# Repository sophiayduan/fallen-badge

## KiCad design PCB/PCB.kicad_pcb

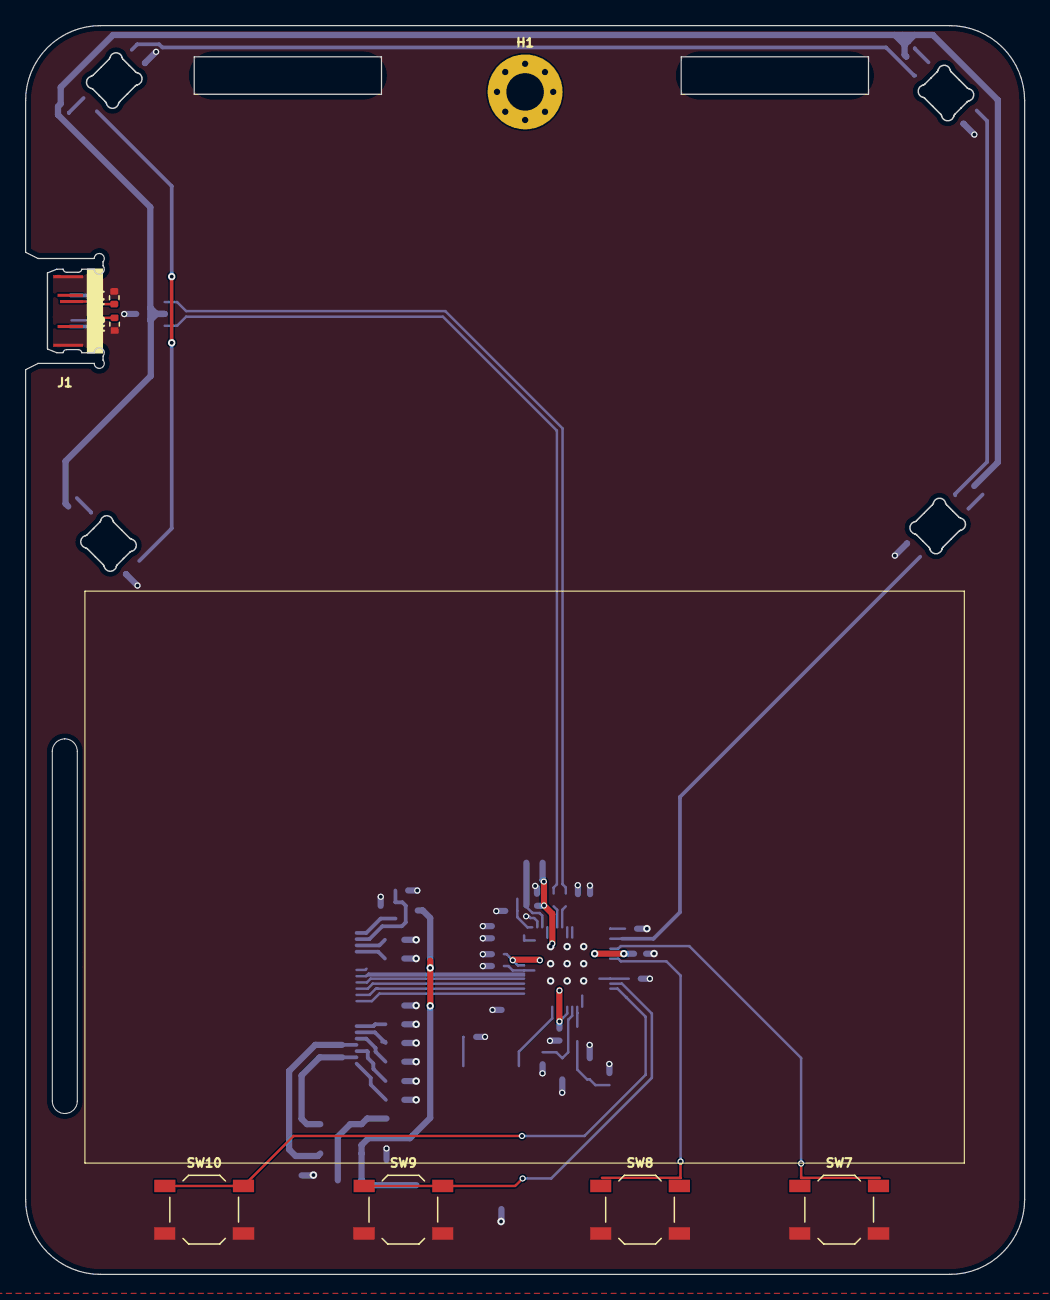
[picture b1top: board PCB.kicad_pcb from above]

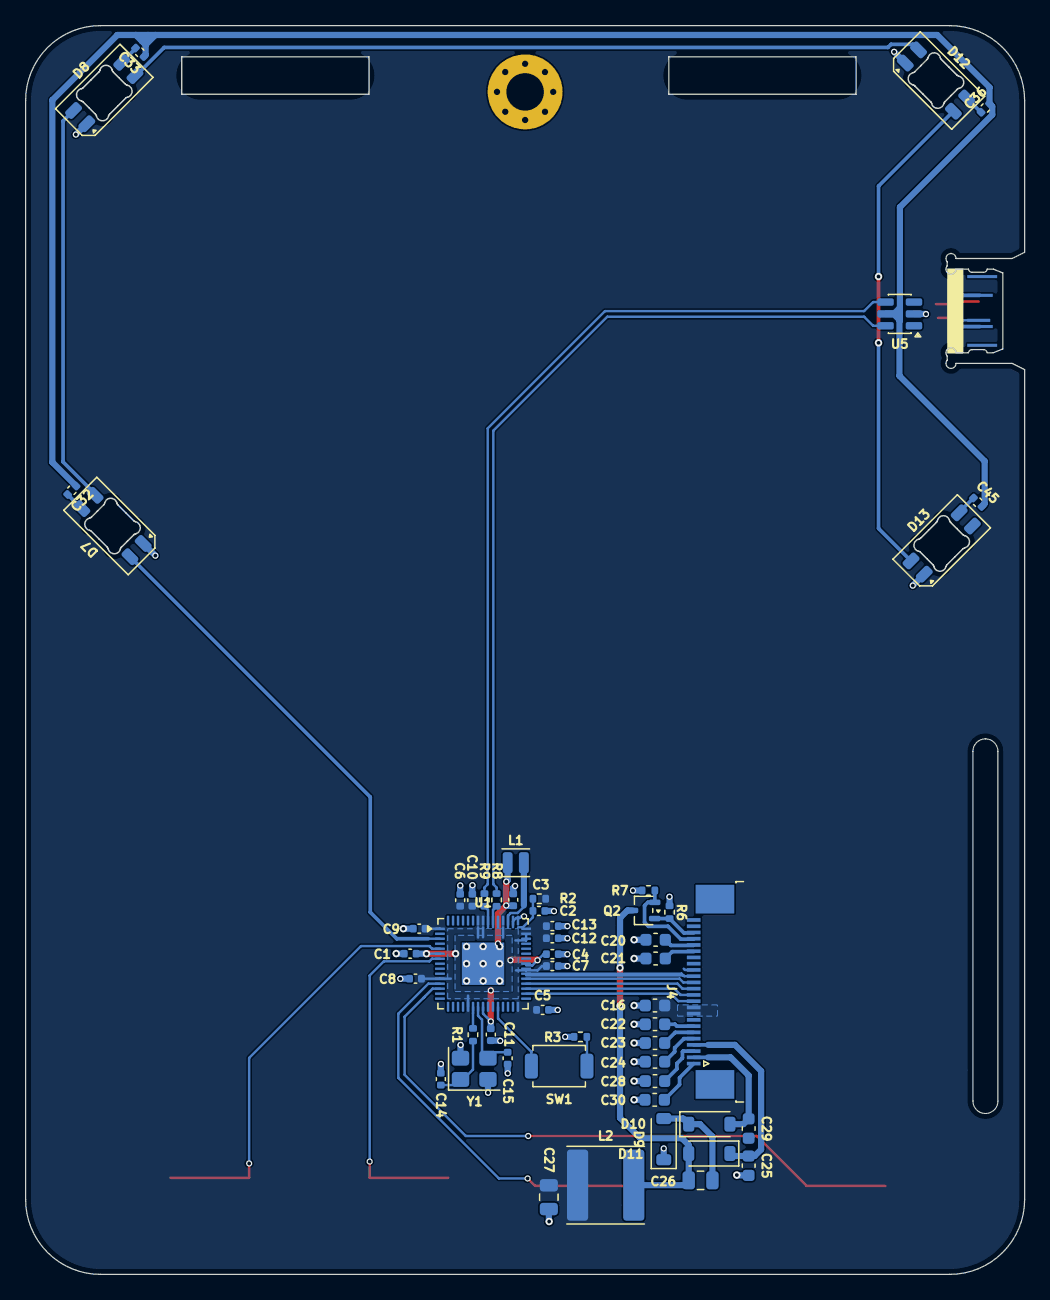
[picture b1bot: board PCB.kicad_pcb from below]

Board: 2 copper layers, 80.0 x 100.0 mm, 61 parts (53 on the bottom side), 49 nets.

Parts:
C1, C3, C4, C5, C7, C8, C9, C10, C12, C13, C32, C33, C36, C45: 100nF; C_0402_1005Metric
C2, C6, C11: 4.7uF; C_0402_1005Metric
C14, C15: 15pF; C_0402_1005Metric
C16: 0.1uF; C_0603_1608Metric
C20, C21, C22, C23, C24, C25, C28, C29, C30: 1uF; C_0603_1608Metric
C26, C27: 4.7uF; C_0805_2012Metric
D7, D8, D12, D13: SK6812; LED_SK6812MINI-E_3.2x2.8mm_P1.5mm_ReverseMount
D9, D10, D11: MBR0530; D_SOD-123
H1: Lanyard Hole; MountingHole_3mm_Pad_Via
J1: USB_C_Receptacle_USB2.0; PCBTypeC_10P
J4: E-INK; TE_2-1734839-4_1x24-1MP_P0.5mm_Horizontal
L1: 3.3uH; L_Changjiang_FTC201610D
L2: 68uH; L_Changjiang_FNR6028S
Q2: Si1308EDL; SOT-323_SC-70
R1: 1k; R_0402_1005Metric
R2: 33R; R_0402_1005Metric
R3: R_Small; R_0402_1005Metric
R4, R5: 5.1k; R_0402_1005Metric
R6: 10k; R_0402_1005Metric
R7: 0.47R; R_0402_1005Metric
R8, R9: 27R; R_0402_1005Metric
SW1: SW_Push; SW_SPST_TS-1088-xR020
SW7, SW8, SW9, SW10: SW_Push; SW_SPST_TL3342
U1: RP2354A; QFN-60-1EP_7x7mm_P0.4mm_EP3.4x3.4mm
U5: USBLC6-2SC6; SOT-23-6
Y1: 12MHz; Crystal_SMD_Abracon_ABM8G-4Pin_3.2x2.5mm

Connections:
+1V1: C1.1, C3.1, C4.1, C11.1, L1.1, U1.6 (DVDD), U1.23 (DVDD), U1.39 (DVDD), U1.50 (VREG_FB)
+3.3V: C5.1, C6.1, C7.1, C8.1, C9.1, C10.1, C12.1, C13.1, C16.2, C27.1, J4.9 (VCI), J4.10 (VDDIO), L2.1, R2.1, U1.1 (IOVDD), U1.11 (IOVDD), U1.20 (IOVDD), U1.30 (IOVDD), U1.38 (IOVDD), U1.44 (ADC_AVDD), U1.45 (IOVDD), U1.49 (VREG_VIN), U1.53 (USB_OTP_VDD), U1.54 (QSPI_IOVDD)
+5V: C32.1, C33.1, C36.1, C45.1, U5.5 (VBUS)
/BUSY: J4.16 (BUSY), U1.37 (GPIO25)
/CS: J4.13 (CS), U1.34 (GPIO22)
/D+: R9.2, U5.4 (I/O2)
/D-: R8.1, U5.6 (I/O1)
/DC: J4.14 (D/C), U1.35 (GPIO23)
/GDR: J4.23 (GDR), Q2.1 (G), R6.1
/GPIO1: D7.2 (DIN), U1.3 (GPIO1)
/GPIO3: SW7.1, U1.5 (GPIO3)
/GPIO4: SW8.1, U1.7 (GPIO4)
/GPIO5: SW9.1, U1.12 (GPIO8)
/GPIO6: SW10.1, U1.13 (GPIO9)
/PREVGH: C25.1, D11.1 (K), J4.4 (VGH)
/PREVGL: C29.1, D10.2 (A), J4.2 (VGL)
/RESE: J4.22 (RESE), Q2.2 (S), R7.1
/RST: J4.15 (RST), U1.36 (GPIO24)
/SPI_MOSI: J4.11 (SDA), U1.32 (GPIO20)
/SPI_SCK: J4.12 (SCL), U1.33 (GPIO21)
GND: C1.2, C2.2, C3.2, C4.2, C5.2, C6.2, C7.2, C8.2, C9.2, C10.2, C11.2, C12.2, C13.2, C14.1, C15.1, C16.1, C20.2, C21.2, C22.2, C23.2, C24.2, C25.2, C27.2, C28.2, C29.2, C30.2, D7.1 (VSS), D8.1 (VSS), D9.1 (K), D12.1 (VSS), D13.1 (VSS), J1.A1 (GND), J1.A12 (GND), J1.B1 (GND), J1.B12 (GND), J4.8 (VSS), J4.17 (BS1), J4.24 (SHIELD), R3.2, R4.2, R5.1, R6.2, R7.2, SW7.2, SW8.2, SW9.2, SW10.2, U1.47 (VREG_PGND), U1.61 (GND), U5.2 (GND), Y1.2 (G), Y1.4 (G)
unnamed: C14.2, R1.1, Y1.1
unnamed: J1.A4 (VBUS), J1.A9 (VBUS), J1.B4 (VBUS), J1.B9 (VBUS)
unnamed: D7.4 (DOUT), D8.2 (DIN)
unnamed: C32.2, D7.3 (VDD)
unnamed: C33.2, D8.3 (VDD)
unnamed: C26.1, D9.2 (A), D10.1 (K)
unnamed: C26.2, D11.2 (A), L2.2, Q2.3 (D)
unnamed: D8.4 (DOUT), D12.2 (DIN)
unnamed: D12.4 (DOUT), D13.2 (DIN)
unnamed: C36.2, D12.3 (VDD)
unnamed: C45.2, D13.3 (VDD)
unnamed: J1.A5 (CC1), R4.1
unnamed: J1.B5 (CC2), R5.2
unnamed: C30.1, J4.1 (VCOM)
unnamed: C22.1, J4.7 (VDD)
unnamed: C20.1, J4.21 (VGL/NC)
unnamed: C23.1, J4.6 (VPP)
unnamed: C24.1, J4.5 (VSH1)
unnamed: C21.1, J4.20 (VSH2)
unnamed: C28.1, J4.3 (VSL)
unnamed: R3.1, SW1.1
unnamed: SW1.2, U1.26 (RUN)
unnamed: R8.2, U1.51 (USB_DM)
unnamed: R9.1, U1.52 (USB_DP)
unnamed: C2.1, R2.2, U1.46 (VREG_AVDD)
unnamed: L1.2, U1.48 (VREG_LX)
unnamed: R1.2, U1.21 (XIN)
unnamed: C15.2, U1.22 (XOUT), Y1.3
